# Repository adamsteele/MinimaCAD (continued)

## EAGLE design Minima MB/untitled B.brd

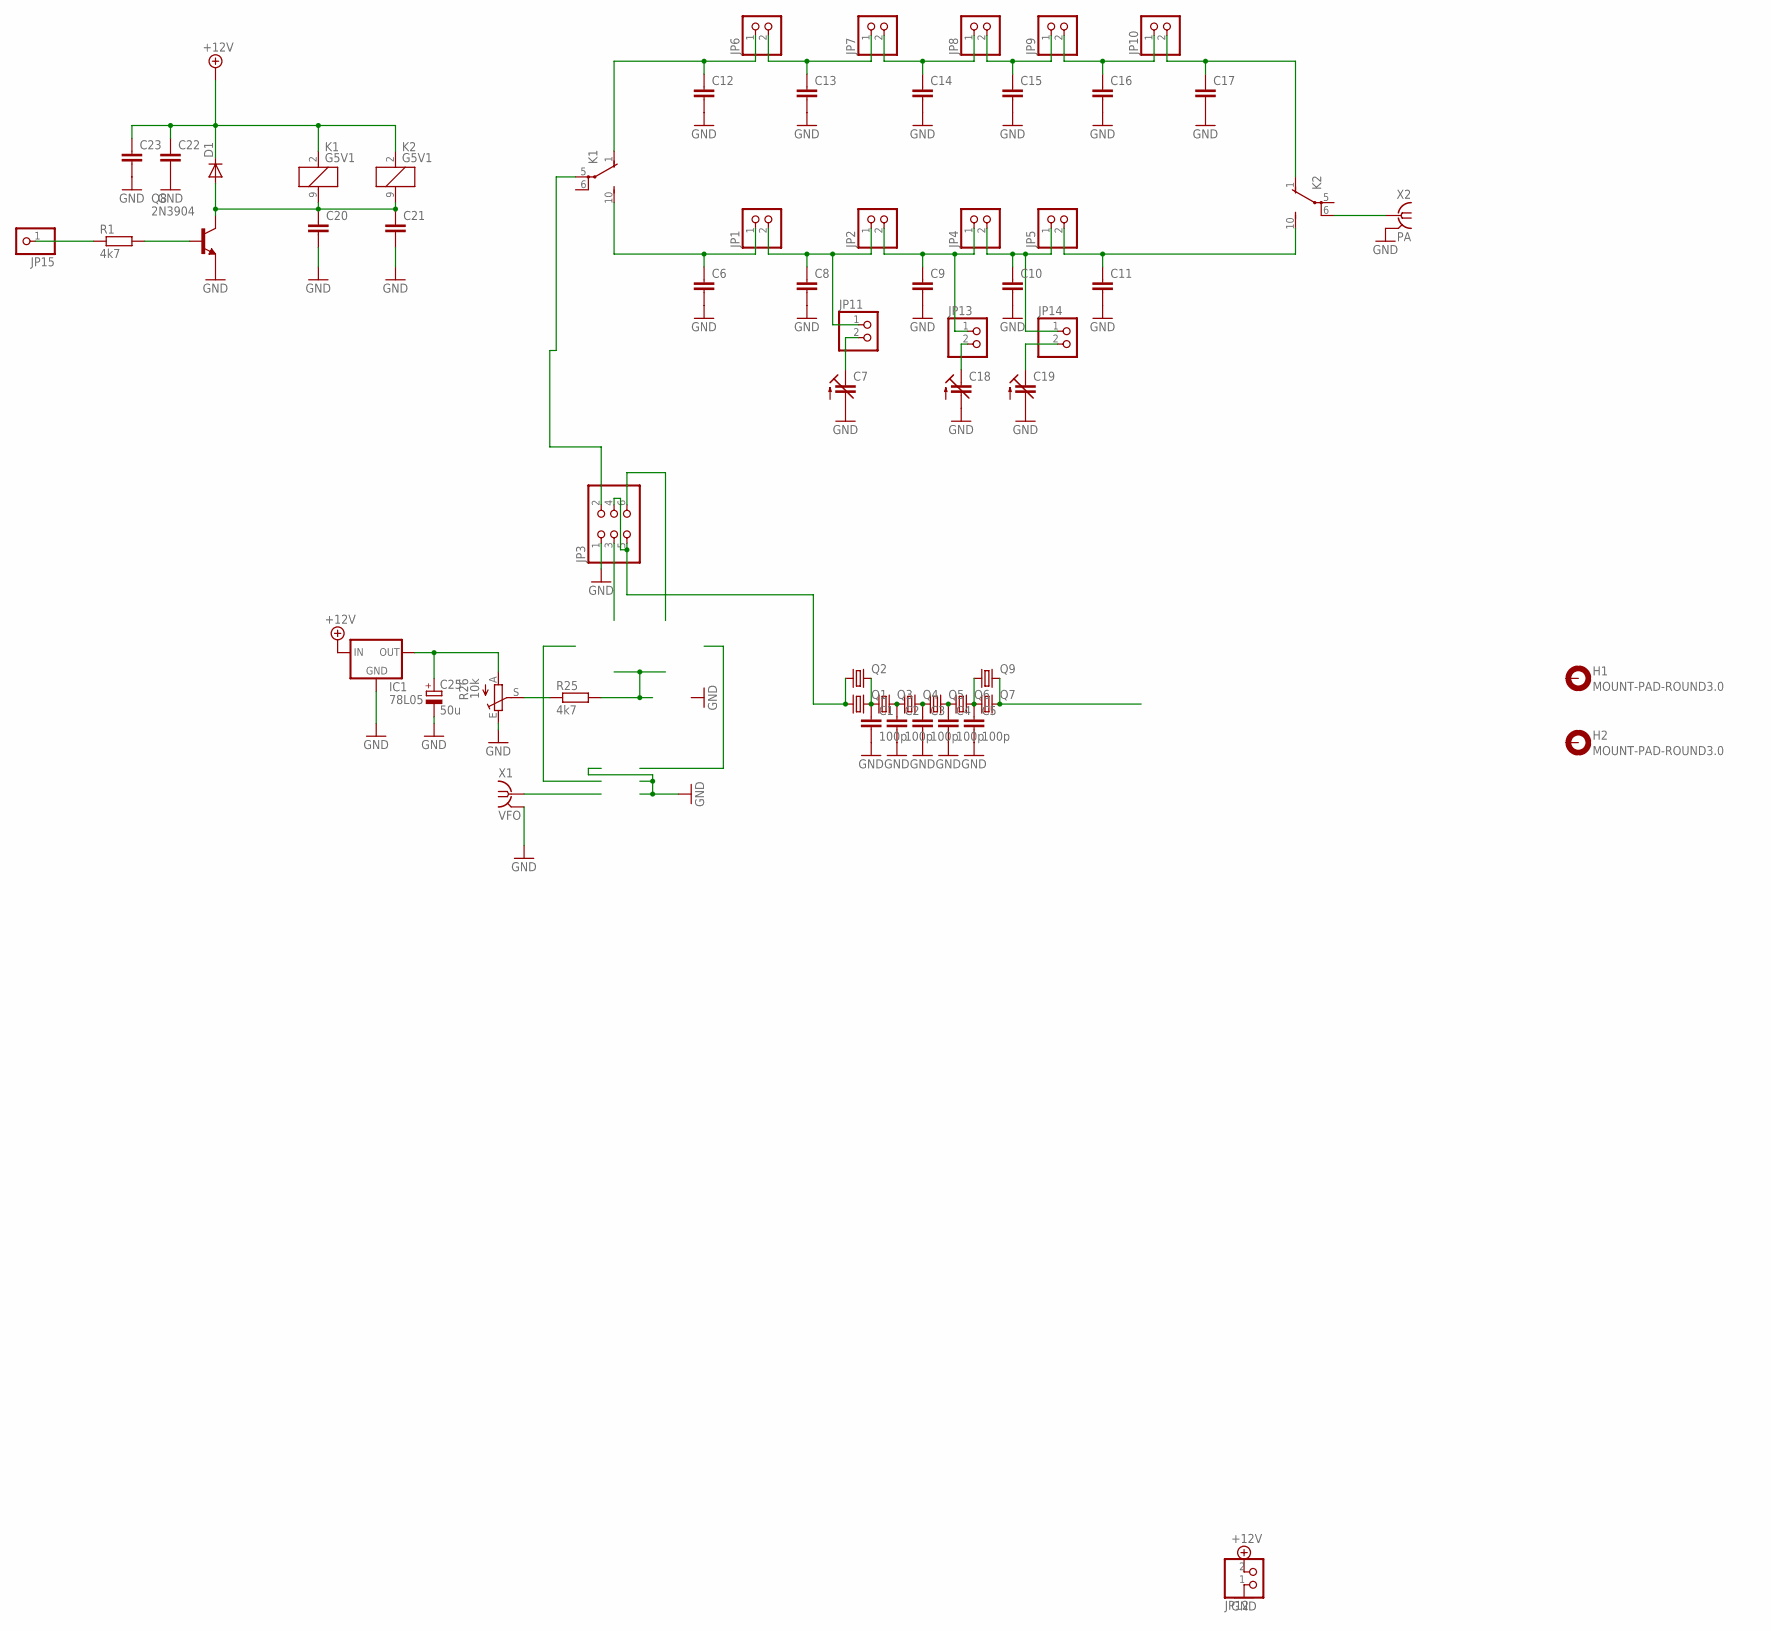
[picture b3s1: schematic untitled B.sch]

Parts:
C1, C2, C3, C4, C5: 100p; C1206
C6, C8, C9, C10, C11, C12, C13, C14, C15, C16, C17, C20, C21, C22, C23: C-EU050-024X044; C050-024X044
C7, C18, C19: C-TRIMMTZ03; CTRIMTZ03
C25: 50u; E2,5-5
D1: DIODE-D-5; D-5
H1, H2: MOUNT-PAD-ROUND3.0; 3,0-PAD
IC1: 78L05; 78LXX
JP1, JP2, JP4, JP5, JP6, JP7, JP8, JP9, JP10, JP11, JP12, JP13, JP14: PINHD-1X2; 1X02
JP3: PINHD-2X3; 2X03
JP15: PINHD-1X1; 1X01
K1, K2: G5V1
Q1, Q2, Q3, Q4, Q5, Q6, Q7, Q9: CRYSTALHC49S; HC49/S
Q8: 2N3904; TO92
R1, R25: 4k7; 0204/5
R26: 10k; CA6V
X1: VFO; BU-SMA-V
X2: PA; BU-SMA-V

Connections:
+12V: C22.1, C23.1, D1.C, IC1.IN, JP12.2, K1.2 (1), K2.2 (1)
GND: C1.2, C2.2, C3.2, C4.2, C5.2, C6.2, C7.2 (A), C8.2, C9.2, C10.2, C11.2, C12.2, C13.2, C14.2, C15.2, C16.2, C17.2, C18.2 (A), C19.2 (A), C20.2, C21.2, C22.2, C23.2, C25.-, IC1.GND, JP3.1, JP12.1, Q8.3 (E), R26.E, X1.2 (GND), X1.3 (GND), X1.4 (GND), X1.5 (GND), X2.2 (GND), X2.3 (GND), X2.4 (GND), X2.5 (GND)
unnamed: C1.1, Q1.2, Q2.2, Q3.1
unnamed: C2.1, Q3.2, Q4.1
unnamed: C3.1, Q4.2, Q5.1
unnamed: C4.1, Q5.2, Q6.1
unnamed: C5.1, Q6.2, Q7.1, Q9.1
unnamed: C6.1, JP1.1, K1.10 (S)
unnamed: Q7.2, Q9.2
unnamed: C8.1, JP1.2, JP2.1, JP11.1
unnamed: C9.1, JP2.2, JP4.1, JP13.1
unnamed: C10.1, JP4.2, JP5.1, JP14.1
unnamed: C11.1, JP5.2, K2.10 (S)
unnamed: C12.1, JP6.1, K1.1 (O)
unnamed: C13.1, JP6.2, JP7.1
unnamed: C14.1, JP7.2, JP8.1
unnamed: C15.1, JP8.2, JP9.1
unnamed: C16.1, JP9.2, JP10.1
unnamed: C17.1, JP10.2, K2.1 (O)
unnamed: Q8.2 (B), R1.2
unnamed: K2.6, X2.1
unnamed: JP3.2, K1.5
unnamed: C7.1 (E), JP11.2
unnamed: C18.1 (E), JP13.2
unnamed: C19.1 (E), JP14.2
unnamed: JP15.1, R1.1
unnamed: C20.1, C21.1, D1.A, K1.9 (2), K2.9 (2), Q8.1 (C)
unnamed: R25.1, R26.S
unnamed: JP3.4, JP3.5, Q1.1, Q2.1
unnamed: C25.+, IC1.OUT, R26.A

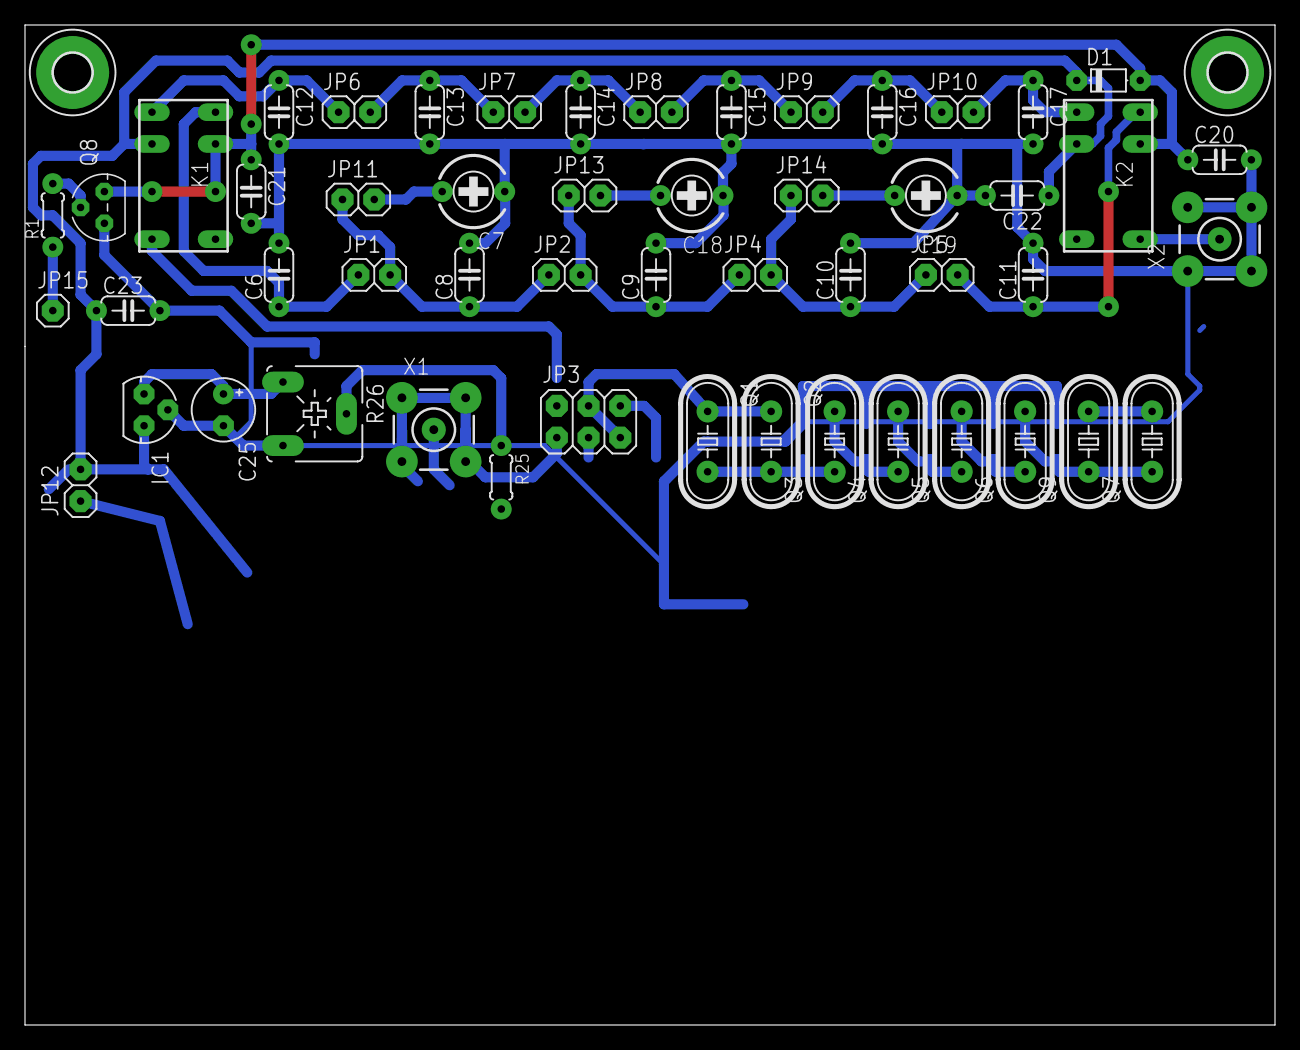
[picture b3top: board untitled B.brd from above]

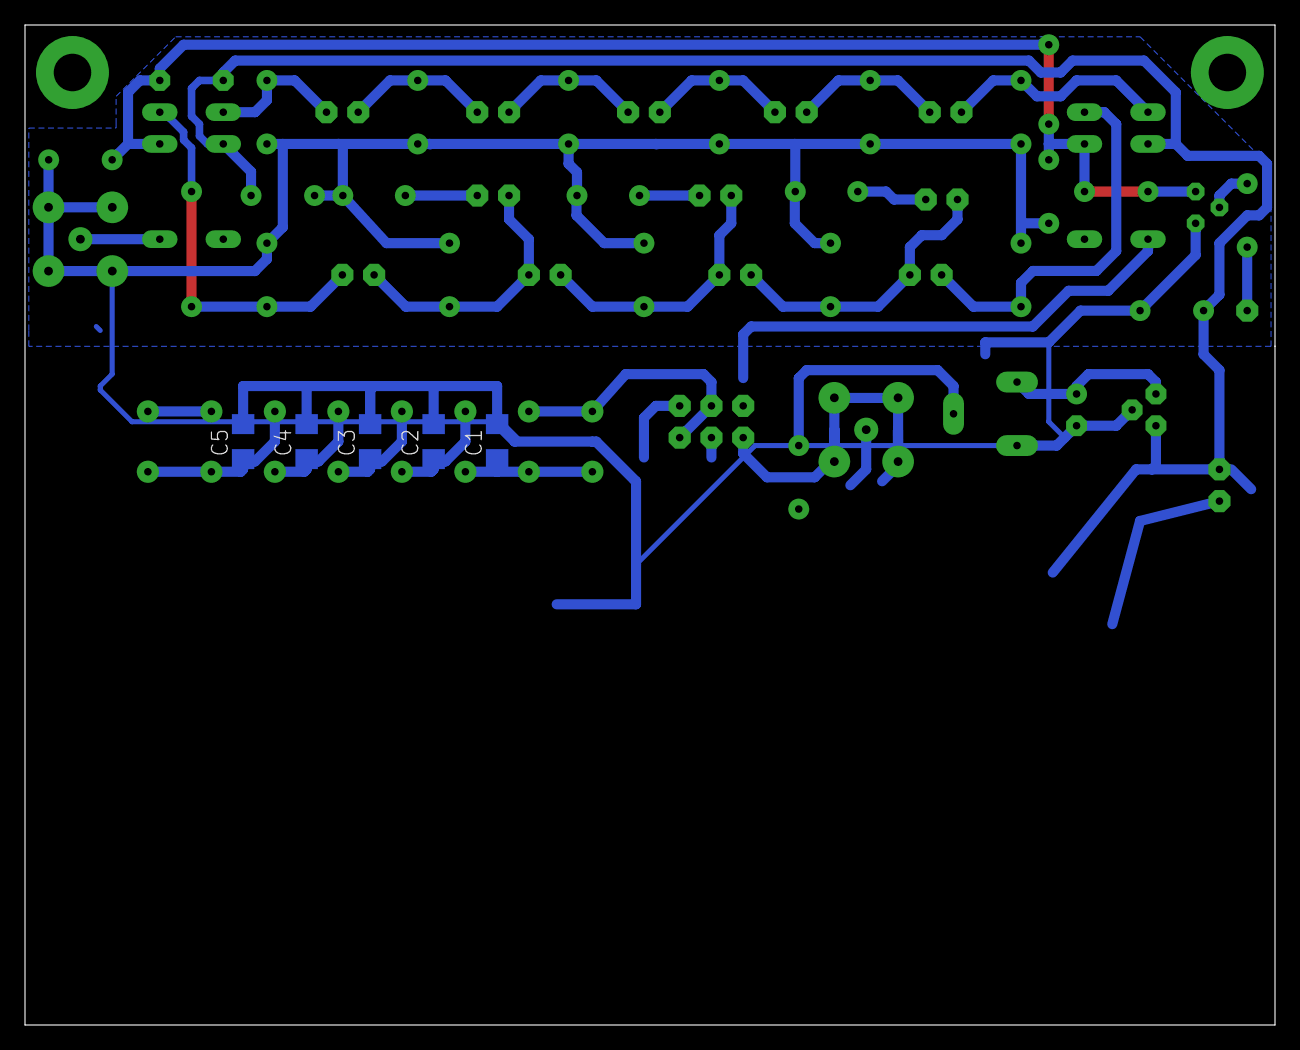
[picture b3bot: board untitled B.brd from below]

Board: 2 copper layers, 100.0 x 80.0 mm, 59 parts (5 on the bottom side), 30 nets.

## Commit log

2014-01-25 Initial commit. Mostly merged the MB together, just need to delete the extra components used to line things up.
2014-01-25 Deleted vestigle components, next I will shuffle the top half of the board back in to place.
2014-01-25 Halves joined, airwires connected, board dimension fixed and GND fill poly redone and added a TOP layer GND fill.
    Added BOMs as well.
2014-01-26 Added BOM files, remove unneeded files.
2014-01-26 READEME.md update
2014-01-27 Saved a copy of the BOMs as CSV
